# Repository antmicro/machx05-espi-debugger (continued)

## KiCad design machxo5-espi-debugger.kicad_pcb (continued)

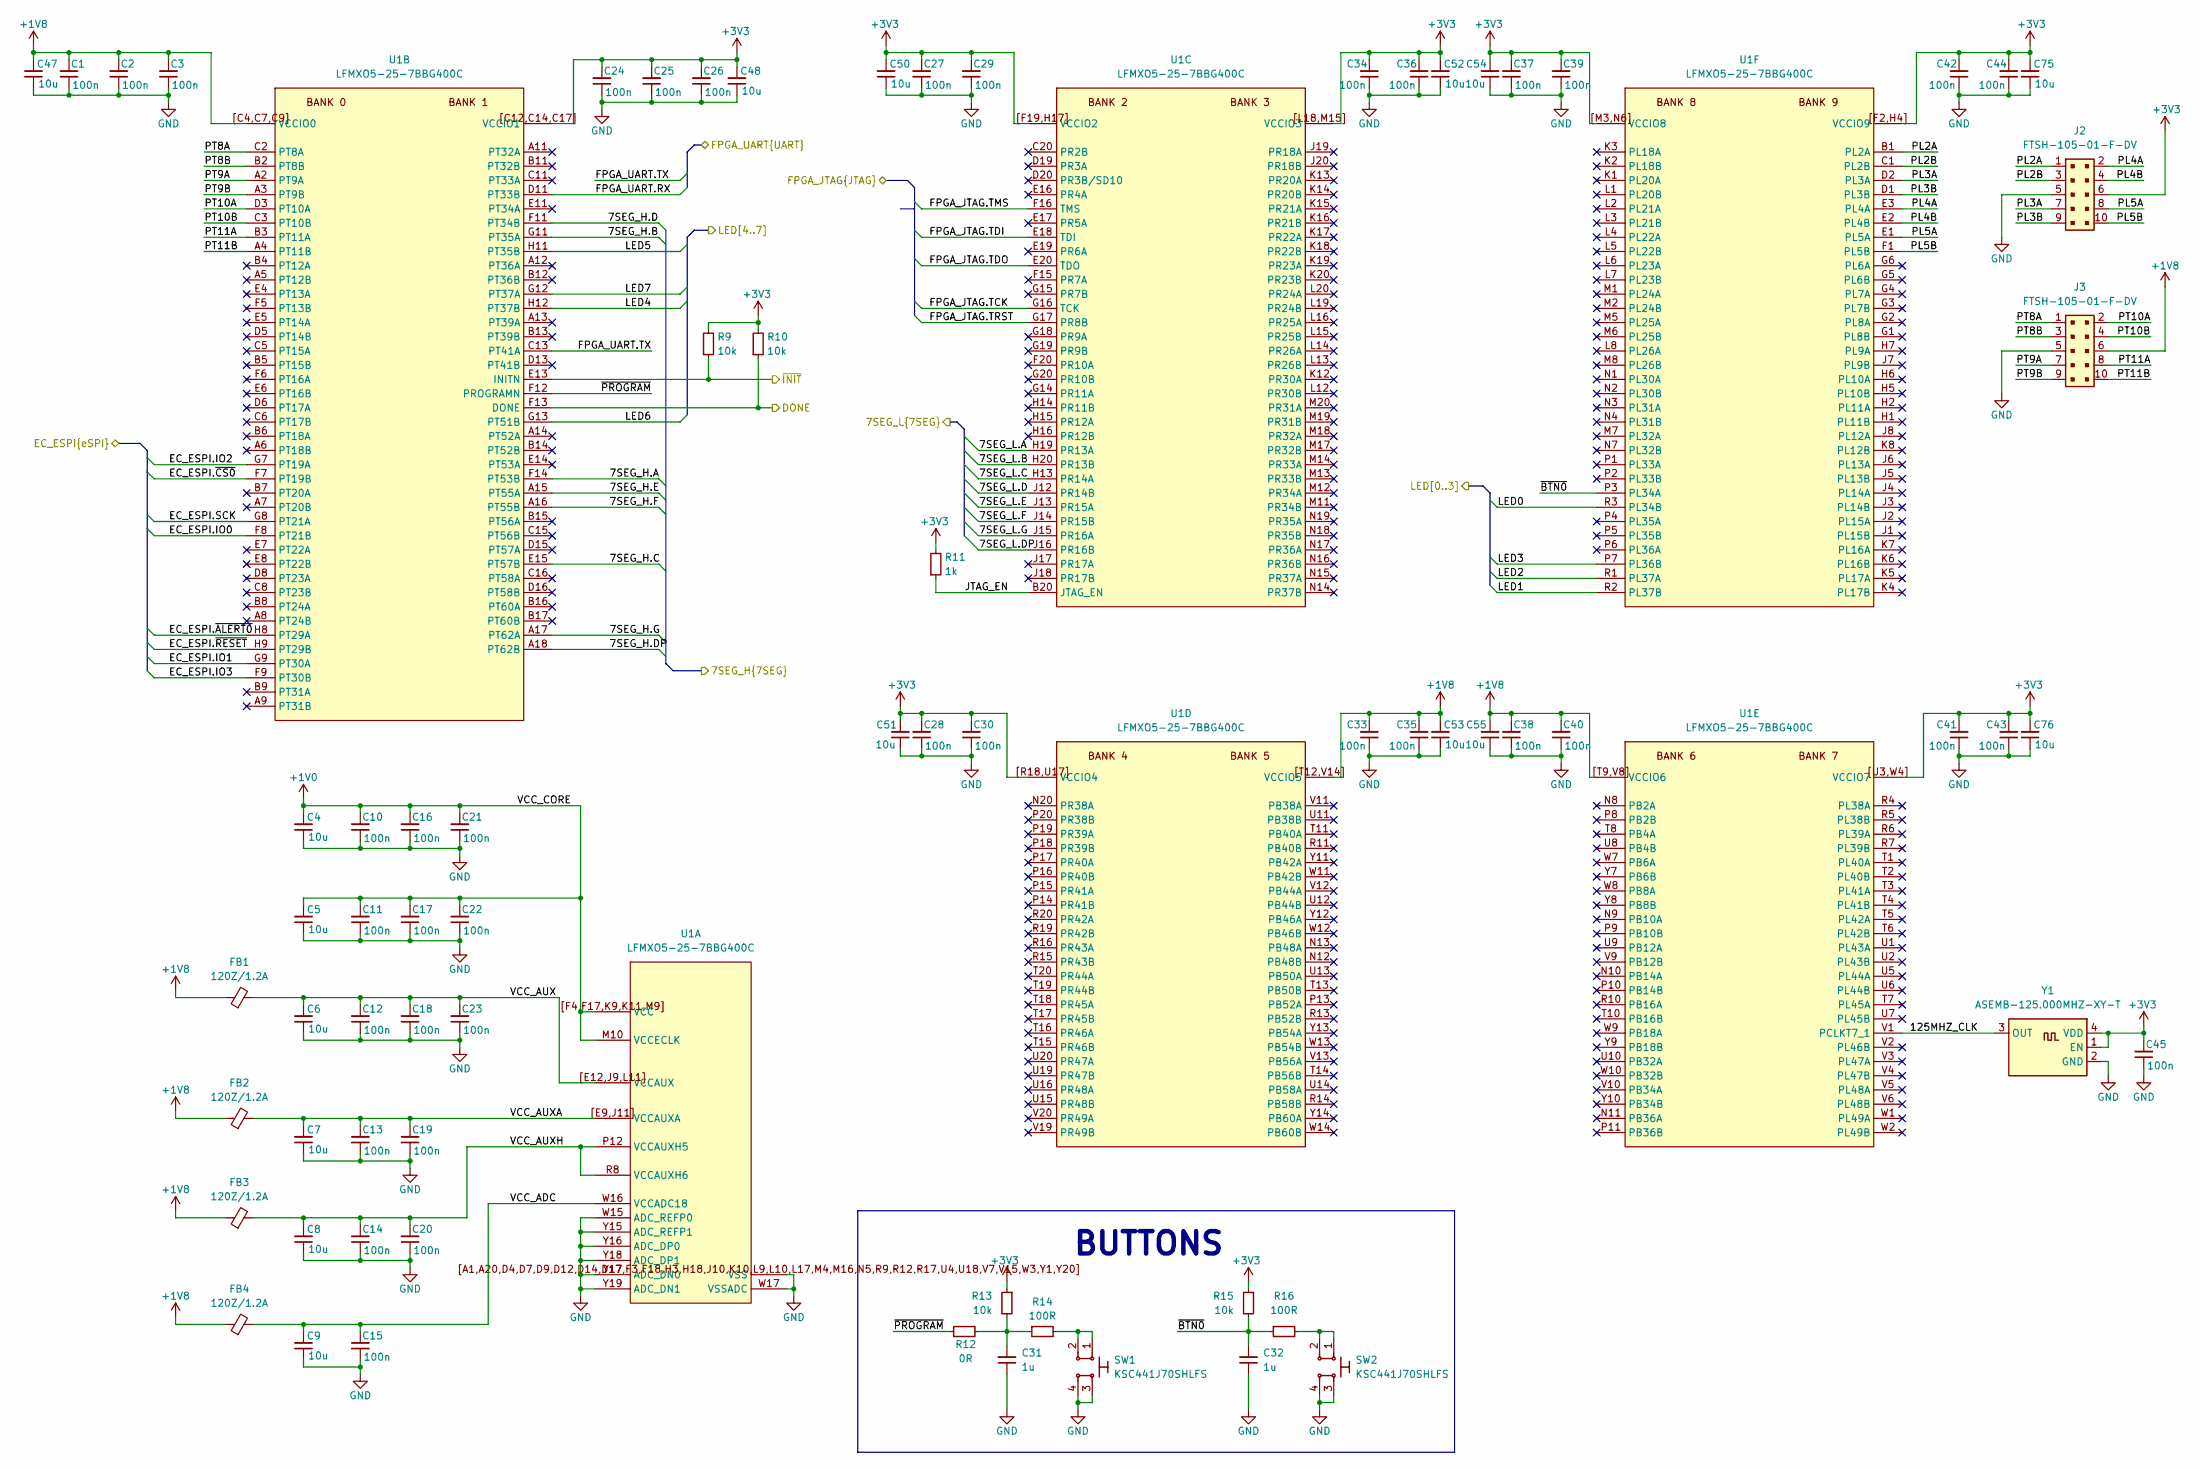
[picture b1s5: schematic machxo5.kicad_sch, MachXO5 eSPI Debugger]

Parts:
C1, C2, C3, C10, C11, C12, C13, C14, C15, C16, C17, C18, C19, C20, C21, C22, C23, C24, C25, C26, C27, C28, C29, C30, C33, C34, C35, C36, C37, C38, C39, C40, C41, C42, C43, C44, C45: C_100n_0402; C_0402_1005Metric; Voltage 50V; MPN GRM155R61H104KE14D
C4, C5, C6, C7, C8, C9, C47, C48, C50, C51, C52, C53, C54, C55, C75, C76: C_10u_6.3V_0402; C_0402_1005Metric; Voltage 6.3V; MPN GRM155R60J106ME15D
C31, C32: C_1u_6.3V_X6S_0402; C_0402_1005Metric; Voltage 6.3V; MPN GRT155C80J105KE01D
FB1, FB2, FB3, FB4: FB_120Z_1.2A_TDK-MPZ_0402; FB_0402_1005Metric; MPN MPZ1005S121CT000
J2, J3: PinHeader_2x5_P1.27mm_SMD; MPN FTSH-105-01-F-DV
R9, R10, R13, R15: R_10k_0402; R_0402_1005Metric; Tolerance 1%; MPN CR0402-FX-1002GLF
R11: R_1k_0402; R_0402_1005Metric; Tolerance 1%; MPN CR0402-FX-1001GLF
R12: R_0R_0402; R_0402_1005Metric; MPN ERJ2GE0R00X
R14, R16: R_100R_0402; R_0402_1005Metric; Tolerance 1%; MPN CR0402-FX-1000GLF
SW1, SW2: SW_KSC441J70SHLFS_SMD; MPN KSC441J70SHLFS
U1: LFMXO5-25-7BBG400C; BGA-400-17x17x0.8mm_Layout20x20_P0.8mm; MPN LFMXO5-25-7BBG400C
Y1: Oscillator_125MHz_ASEMB; Oscillator_SMD_Abracon_ASEMB_3.2x2.5mm; MPN ASEMB-125.000MHZ-XY-T

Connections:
+1V0: C4.2, C5.2, C10.2, C11.2, C16.2, C17.2, C21.2, C22.2, U1.F4 (VCC), U1.F17 (VCC), U1.K9 (VCC), U1.K11 (VCC), U1.M9 (VCC), U1.M10 (VCCECLK), U1.[F4,F17,K9,K11,M9] (VCC); also elsewhere on the board
+1V8: C1.2, C2.2, C3.2, C33.2, C35.2, C38.2, C40.2, C47.2, C53.2, C55.2, FB1.1, FB2.1, FB3.1, FB4.1, J3.6, U1.C4 (VCCIO0), U1.C7 (VCCIO0), U1.C9 (VCCIO0), U1.T9 (VCCIO6), U1.T12 (VCCIO5), U1.V8 (VCCIO6), U1.V14 (VCCIO5), U1.[C4,C7,C9] (VCCIO0), U1.[T9,V8] (VCCIO6), U1.[T12,V14] (VCCIO5); also elsewhere on the board
+3V3: C24.2, C25.2, C26.2, C27.2, C28.2, C29.2, C30.2, C34.2, C36.2, C37.2, C39.2, C41.2, C42.2, C43.2, C44.2, C45.2, C48.2, C50.2, C51.2, C52.2, C54.2, C75.2, C76.2, J2.6, R9.2, R10.2, R11.2, R13.1, R15.1, U1.C12 (VCCIO1), U1.C14 (VCCIO1), U1.C17 (VCCIO1), U1.F2 (VCCIO9), U1.F19 (VCCIO2), U1.H4 (VCCIO9), U1.H17 (VCCIO2), U1.L18 (VCCIO3), U1.M3 (VCCIO8), U1.M15 (VCCIO3), U1.N6 (VCCIO8), U1.R18 (VCCIO4), U1.U3 (VCCIO7), U1.U17 (VCCIO4), U1.W4 (VCCIO7), U1.[C12,C14,C17] (VCCIO1), U1.[F2,H4] (VCCIO9), U1.[F19,H17] (VCCIO2), U1.[L18,M15] (VCCIO3), U1.[M3,N6] (VCCIO8), U1.[R18,U17] (VCCIO4), U1.[U3,W4] (VCCIO7), Y1.1 (EN), Y1.4 (VDD); also elsewhere on the board
/DC-SCM Interposer connector/EC_ESPI.IO0: U1.F8 (PT21B); also elsewhere on the board
/DC-SCM Interposer connector/EC_ESPI.IO1: U1.G9 (PT30A); also elsewhere on the board
/DC-SCM Interposer connector/EC_ESPI.IO2: U1.G7 (PT19A); also elsewhere on the board
/DC-SCM Interposer connector/EC_ESPI.IO3: U1.F9 (PT30B); also elsewhere on the board
/DC-SCM Interposer connector/EC_ESPI.SCK: U1.G8 (PT21A); also elsewhere on the board
/DC-SCM Interposer connector/EC_ESPI.~ALERT0: U1.H8 (PT29A); also elsewhere on the board
/DC-SCM Interposer connector/EC_ESPI.~CS0: U1.F7 (PT19B); also elsewhere on the board
/DC-SCM Interposer connector/EC_ESPI.~RESET: U1.H9 (PT29B); also elsewhere on the board
/MachXO5/7SEG_H.A: U1.F14 (PT53B); also elsewhere on the board
/MachXO5/7SEG_H.B: U1.G11 (PT35A); also elsewhere on the board
/MachXO5/7SEG_H.C: U1.E15 (PT57B); also elsewhere on the board
/MachXO5/7SEG_H.D: U1.F11 (PT34B); also elsewhere on the board
/MachXO5/7SEG_H.DP: U1.A18 (PT62B); also elsewhere on the board
/MachXO5/7SEG_H.E: U1.A15 (PT55A); also elsewhere on the board
/MachXO5/7SEG_H.F: U1.A16 (PT55B); also elsewhere on the board
/MachXO5/7SEG_H.G: U1.A17 (PT62A); also elsewhere on the board
/MachXO5/7SEG_L.A: U1.H19 (PR13A); also elsewhere on the board
/MachXO5/7SEG_L.B: U1.H20 (PR13B); also elsewhere on the board
/MachXO5/7SEG_L.C: U1.H13 (PR14A); also elsewhere on the board
/MachXO5/7SEG_L.D: U1.J12 (PR14B); also elsewhere on the board
/MachXO5/7SEG_L.DP: U1.J16 (PR16B); also elsewhere on the board
/MachXO5/7SEG_L.E: U1.J13 (PR15A); also elsewhere on the board
/MachXO5/7SEG_L.F: U1.J14 (PR15B); also elsewhere on the board
/MachXO5/7SEG_L.G: U1.J15 (PR16A); also elsewhere on the board
/MachXO5/125MHZ_CLK: U1.V1 (PCLKT7_1), Y1.3 (OUT)
/MachXO5/DONE: R10.1, U1.F13 (DONE); also elsewhere on the board
/MachXO5/FPGA_JTAG.TCK: U1.G16 (TCK); also elsewhere on the board
/MachXO5/FPGA_JTAG.TDI: U1.E18 (TDI); also elsewhere on the board
/MachXO5/FPGA_JTAG.TDO: U1.E20 (TDO); also elsewhere on the board
/MachXO5/FPGA_JTAG.TMS: U1.F16 (TMS); also elsewhere on the board
/MachXO5/FPGA_JTAG.TRST: U1.G17 (PR8B); also elsewhere on the board
/MachXO5/FPGA_UART.RX: U1.D11 (PT33B); also elsewhere on the board
/MachXO5/FPGA_UART.TX: U1.C13 (PT41A); also elsewhere on the board
/MachXO5/JTAG_EN: R11.1, U1.B20 (JTAG_EN)
/MachXO5/LED0: U1.R3 (PL34B); also elsewhere on the board
/MachXO5/LED1: U1.R2 (PL37B); also elsewhere on the board
/MachXO5/LED2: U1.R1 (PL37A); also elsewhere on the board
/MachXO5/LED3: U1.P7 (PL36B); also elsewhere on the board
/MachXO5/LED4: U1.H12 (PT37B); also elsewhere on the board
/MachXO5/LED5: U1.H11 (PT35B); also elsewhere on the board
/MachXO5/LED6: U1.G13 (PT51B); also elsewhere on the board
/MachXO5/LED7: U1.G12 (PT37A); also elsewhere on the board
/MachXO5/PL2A: J2.1, U1.B1 (PL2A)
/MachXO5/PL2B: J2.3, U1.C1 (PL2B)
/MachXO5/PL3A: J2.7, U1.D2 (PL3A)
/MachXO5/PL3B: J2.9, U1.D1 (PL3B)
/MachXO5/PL4A: J2.2, U1.E3 (PL4A)
/MachXO5/PL4B: J2.4, U1.E2 (PL4B)
/MachXO5/PL5A: J2.8, U1.E1 (PL5A)
/MachXO5/PL5B: J2.10, U1.F1 (PL5B)
/MachXO5/PT8A: J3.1, U1.C2 (PT8A)
/MachXO5/PT8B: J3.3, U1.B2 (PT8B)
/MachXO5/PT9A: J3.7, U1.A2 (PT9A)
/MachXO5/PT9B: J3.9, U1.A3 (PT9B)
/MachXO5/PT10A: J3.2, U1.D3 (PT10A)
/MachXO5/PT10B: J3.4, U1.C3 (PT10B)
/MachXO5/PT11A: J3.8, U1.B3 (PT11A)
/MachXO5/PT11B: J3.10, U1.A4 (PT11B)
/MachXO5/VCC_ADC: C9.2, C15.2, FB4.2, U1.W16 (VCCADC18)
/MachXO5/VCC_AUX: C6.2, C12.2, C18.2, C23.2, FB1.2, U1.E12 (VCCAUX), U1.J9 (VCCAUX), U1.L11 (VCCAUX), U1.[E12,J9,L11] (VCCAUX)
/MachXO5/VCC_AUXA: C7.2, C13.2, C19.2, FB2.2, U1.E9 (VCCAUXA), U1.J11 (VCCAUXA), U1.[E9,J11] (VCCAUXA)
/MachXO5/VCC_AUXH: C8.2, C14.2, C20.2, FB3.2, U1.P12 (VCCAUXH5), U1.R8 (VCCAUXH6)
/MachXO5/~BTN0: C32.2, R15.2, R16.1, U1.P3 (PL34A)
/MachXO5/~INIT: R9.1, U1.E13 (INITN); also elsewhere on the board
/MachXO5/~PROGRAM: R12.1, U1.F12 (PROGRAMN)
GND: C1.1, C2.1, C3.1, C4.1, C5.1, C6.1, C7.1, C8.1, C9.1, C10.1, C11.1, C12.1, C13.1, C14.1, C15.1, C16.1, C17.1, C18.1, C19.1, C20.1, C21.1, C22.1, C23.1, C24.1, C25.1, C26.1, C27.1, C28.1, C29.1, C30.1, C31.1, C32.1, C33.1, C34.1, C35.1, C36.1, C37.1, C38.1, C39.1, C40.1, C41.1, C42.1, C43.1, C44.1, C45.1, C47.1, C48.1, C50.1, C51.1, C52.1, C53.1, C54.1, C55.1, C75.1, C76.1, J2.5, J3.5, SW1.3, SW1.4, SW2.3, SW2.4, U1.A1 (VSS), U1.A20 (VSS), U1.D4 (VSS), U1.D7 (VSS), U1.D9 (VSS), U1.D12 (VSS), U1.D14 (VSS), U1.D17 (VSS), U1.F3 (VSS), U1.F18 (VSS), U1.H3 (VSS), U1.H18 (VSS), U1.J10 (VSS), U1.K10 (VSS), U1.L9 (VSS), U1.L10 (VSS), U1.L17 (VSS), U1.M4 (VSS), U1.M16 (VSS), U1.N5 (VSS), U1.R9 (VSS), U1.R12 (VSS), U1.R17 (VSS), U1.U4 (VSS), U1.U18 (VSS), U1.V7 (VSS), U1.V15 (VSS), U1.W3 (VSS), U1.W15 (ADC_REFP0), U1.W17 (VSSADC), U1.Y1 (VSS), U1.Y15 (ADC_REFP1), U1.Y16 (ADC_DP0), U1.Y17 (ADC_DN0), U1.Y18 (ADC_DP1), U1.Y19 (ADC_DN1), U1.Y20 (VSS), U1.[A1,A20,D4,D7,D9,D1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 (VSS), Y1.2 (GND); also elsewhere on the board
unnamed: C31.2, R12.2, R13.2, R14.1
unnamed: R14.2, SW1.1, SW1.2
unnamed: R16.2, SW2.1, SW2.2

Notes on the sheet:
BUTTONS

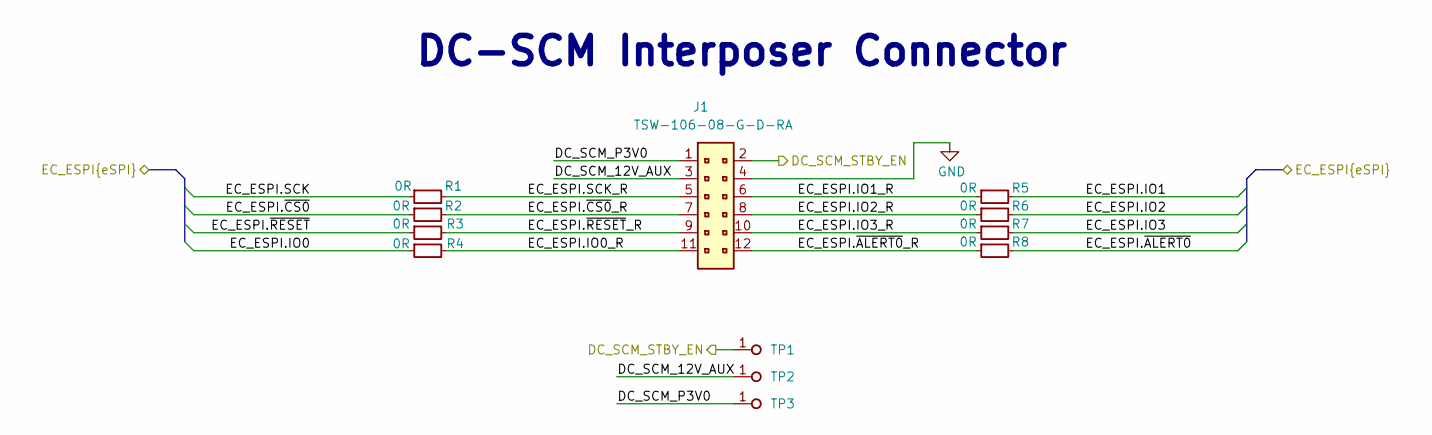
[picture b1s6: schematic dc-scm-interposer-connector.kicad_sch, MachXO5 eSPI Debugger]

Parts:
J1: PinHeader_2x6_P2.54mm_Drill1.1mm_Horizontal; PinHeader_2x6_P2.54mm_Drill1.1mm_Horizontal_ALT; MPN TSW-106-08-G-D-RA
R1, R2, R3, R4, R5, R6, R7, R8: R_0R_0402; R_0402_1005Metric; MPN ERJ2GE0R00X
TP1, TP2, TP3: TP_1mm_SMD; TP_SMD_1mm

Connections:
/DC-SCM Interposer connector/DC_SCM_12V_AUX: J1.3, TP2.1 (1_1)
/DC-SCM Interposer connector/DC_SCM_P3V0: J1.1, TP3.1 (1_1)
/DC-SCM Interposer connector/DC_SCM_STBY_EN: J1.2, TP1.1 (1_1); also elsewhere on the board
/DC-SCM Interposer connector/EC_ESPI.IO0: R4.1; also elsewhere on the board
/DC-SCM Interposer connector/EC_ESPI.IO0_R: J1.11, R4.2
/DC-SCM Interposer connector/EC_ESPI.IO1: R5.2; also elsewhere on the board
/DC-SCM Interposer connector/EC_ESPI.IO1_R: J1.6, R5.1
/DC-SCM Interposer connector/EC_ESPI.IO2: R6.2; also elsewhere on the board
/DC-SCM Interposer connector/EC_ESPI.IO2_R: J1.8, R6.1
/DC-SCM Interposer connector/EC_ESPI.IO3: R7.2; also elsewhere on the board
/DC-SCM Interposer connector/EC_ESPI.IO3_R: J1.10, R7.1
/DC-SCM Interposer connector/EC_ESPI.SCK: R1.1; also elsewhere on the board
/DC-SCM Interposer connector/EC_ESPI.SCK_R: J1.5, R1.2
/DC-SCM Interposer connector/EC_ESPI.~ALERT0: R8.2; also elsewhere on the board
/DC-SCM Interposer connector/EC_ESPI.~ALERT0_R: J1.12, R8.1
/DC-SCM Interposer connector/EC_ESPI.~CS0: R2.1; also elsewhere on the board
/DC-SCM Interposer connector/EC_ESPI.~CS0_R: J1.7, R2.2
/DC-SCM Interposer connector/EC_ESPI.~RESET: R3.1; also elsewhere on the board
/DC-SCM Interposer connector/EC_ESPI.~RESET_R: J1.9, R3.2
GND: J1.4; also elsewhere on the board

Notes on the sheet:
DC-SCM Interposer Connector

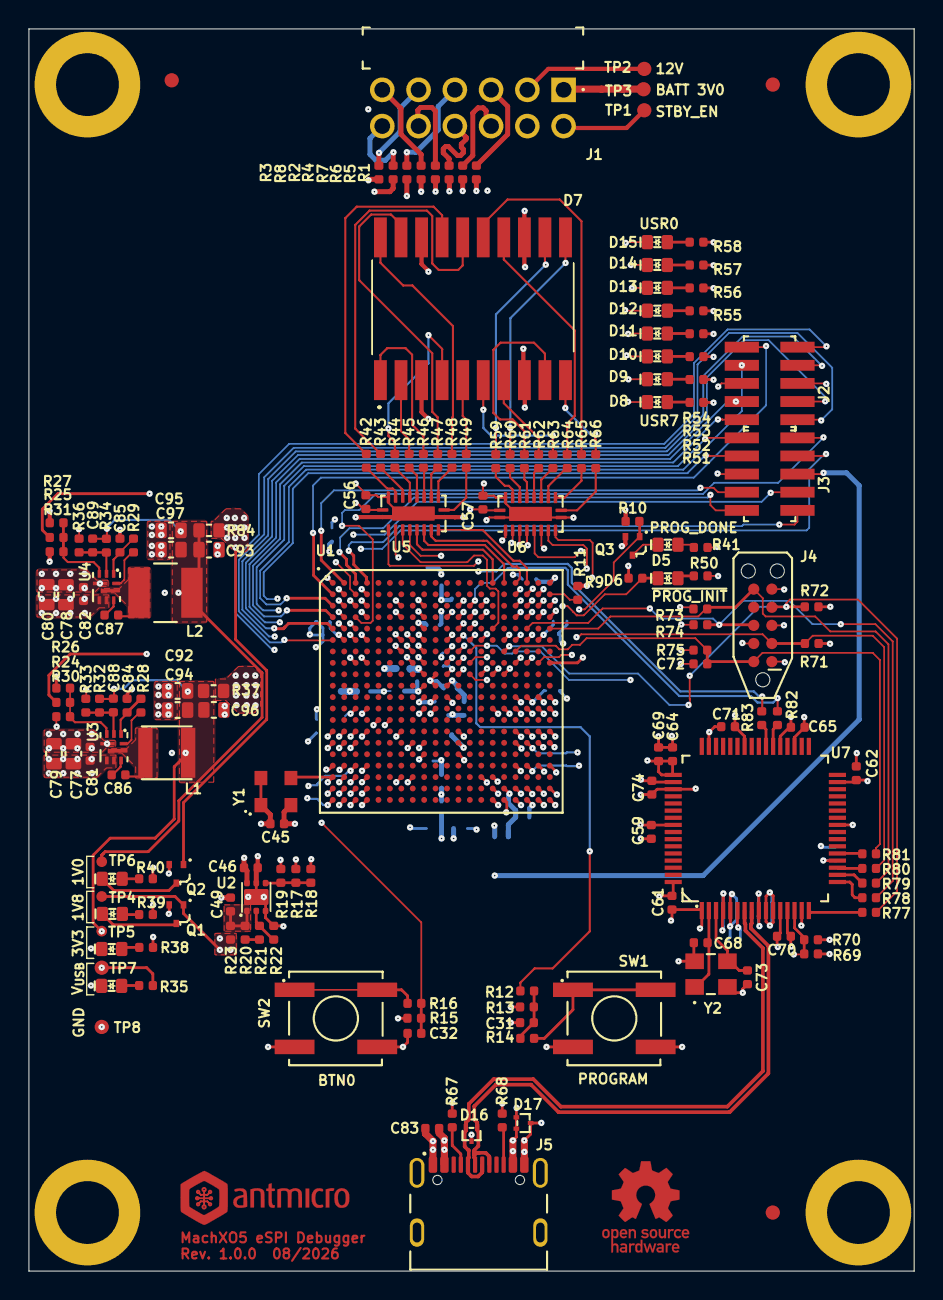
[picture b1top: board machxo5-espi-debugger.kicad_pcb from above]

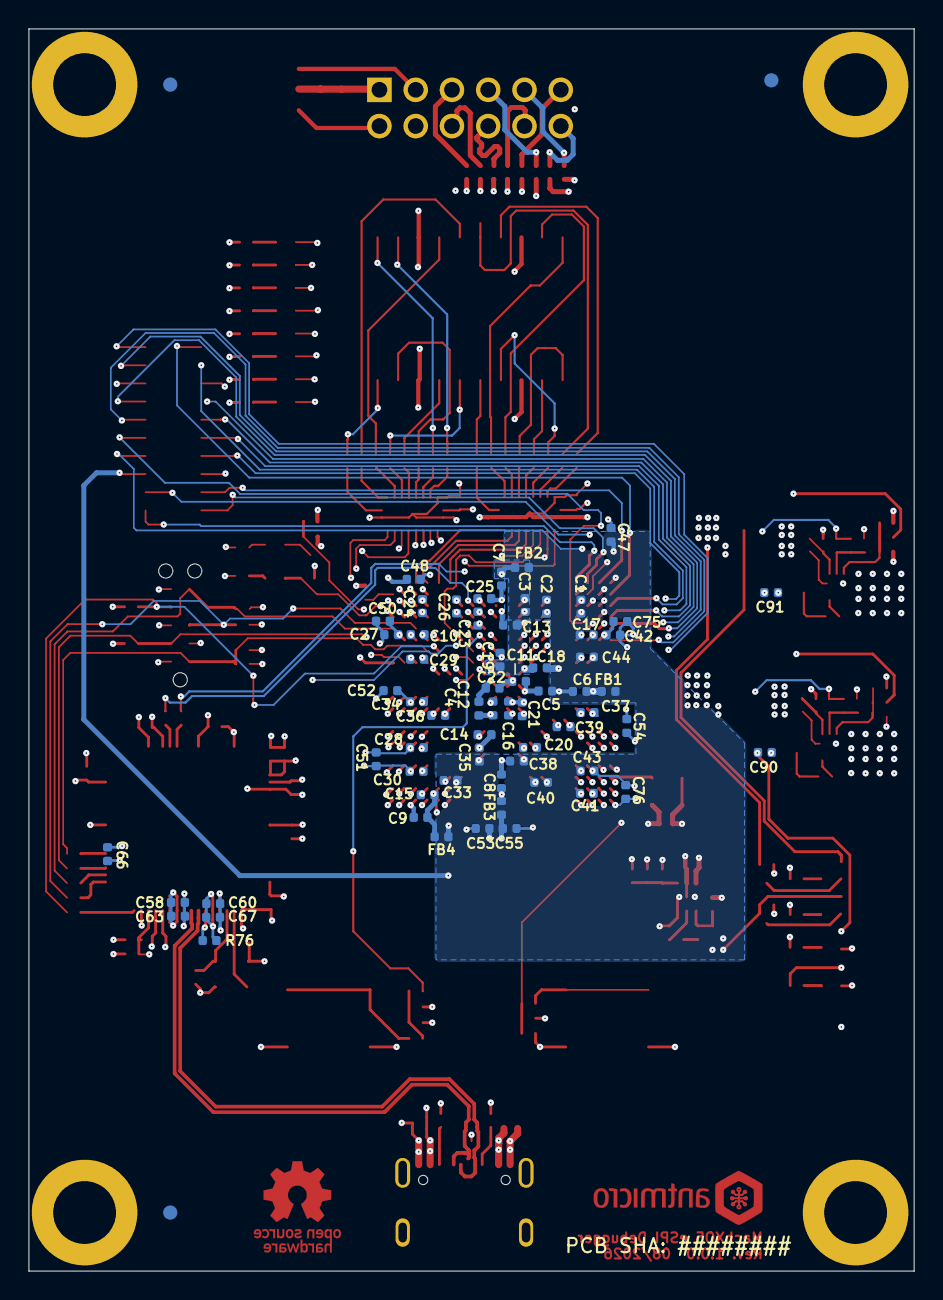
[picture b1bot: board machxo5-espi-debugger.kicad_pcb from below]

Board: 6 copper layers, 62.0 x 87.0 mm, 243 parts (71 on the bottom side), 167 nets.
